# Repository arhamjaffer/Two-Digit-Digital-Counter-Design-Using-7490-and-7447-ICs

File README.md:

# 🔢 Two-Digit Digital Counter Using 7490 & 7447 ICs

<div align="center">

</div>

---

## 📌 Project Overview

This project implements a two-digit decimal counter capable of counting from **00 to 99** using TTL logic ICs.

The design utilizes:

- 7490 Decade Counter IC
- 7447 BCD to Seven Segment Decoder IC
- Common Anode Seven Segment Displays

The counter automatically increments and displays the count on two seven-segment displays.

---

## ⚙️ Components Used

| Component | Quantity |
|------------|----------|
| 7490 Decade Counter IC | 2 |
| 7447 Decoder Driver IC | 2 |
| Common Anode Seven Segment Display | 2 |
| Clock Source | 1 |
| Resistors | Multiple |
| Power Supply (5V) | 1 |

---

## ✨ Features

- Counts from 00 to 99
- Automatic carry generation
- TTL Logic Implementation
- Seven Segment Display Output
- Educational Digital Electronics Project
- Expandable to Higher Digits

---

## 🧠 Working Principle

### Units Counter

The first 7490 counts clock pulses from 0 to 9.

### Tens Counter

After every 10 counts, a carry pulse increments the second 7490.

### Display Driver

Each 7447 converts BCD output into signals for the seven-segment displays.

This allows the count to be displayed as:

```text
00 → 01 → 02 → ... → 98 → 99
```

---

## 📷 Project Gallery

<h2 align="center">📷 Project Gallery</h2>

<h3 align="center">Circuit Schematic</h3>

<h3 align="center">PCB Layout</h3>

<h3 align="center">3D PCB Views</h3>

<table align="center">
<tr>
<td align="center">
<br>
<b>Front View</b>
</td>

<td align="center">
<br>
<b>Back View</b>
</td>
</tr>
</table>
---

## 🎯 Learning Outcomes

✔ Digital Logic Design

✔ BCD Counting

✔ Seven Segment Display Interfacing

✔ TTL Logic Circuits

✔ Hardware Troubleshooting

✔ PCB Design

---

## 🚀 Applications

- Digital Counters
- Frequency Counters
- Event Counters
- Educational Electronics Labs
- Embedded System Prototyping

---

## 👨‍💻 Author

### Arham Jaffer

Electrical Engineering Student

PCB Designer | Embedded Systems Developer | IoT Enthusiast

---

⭐ If you found this project useful, please consider giving it a star.

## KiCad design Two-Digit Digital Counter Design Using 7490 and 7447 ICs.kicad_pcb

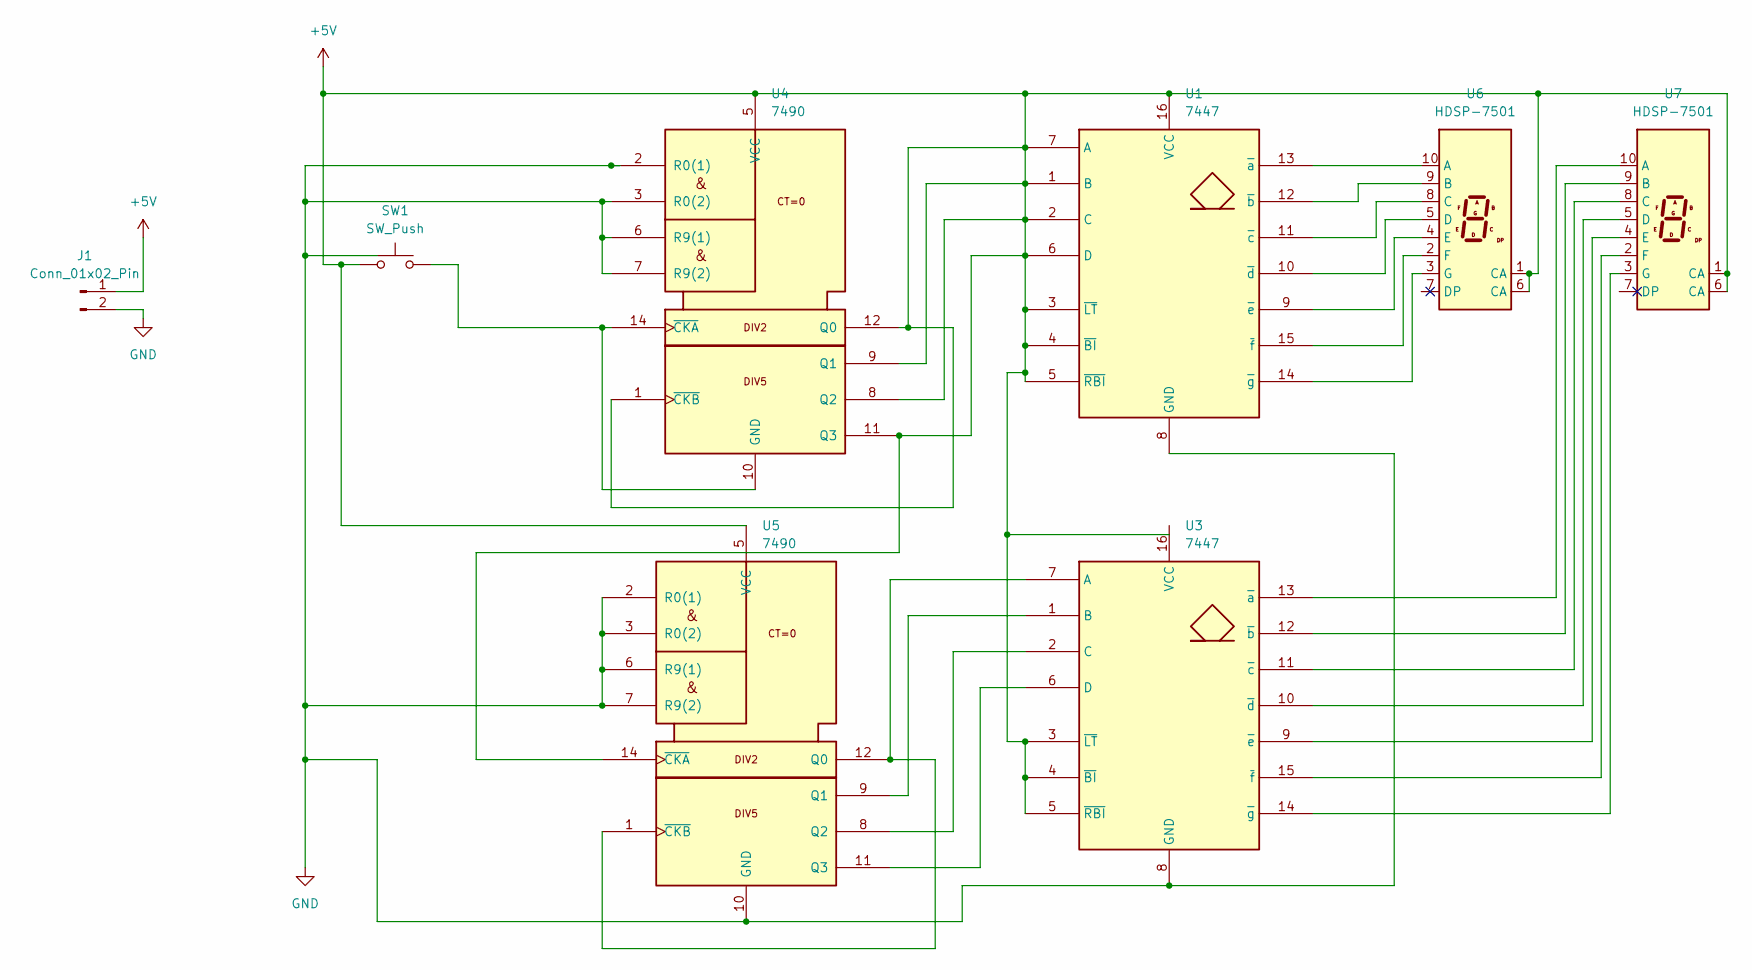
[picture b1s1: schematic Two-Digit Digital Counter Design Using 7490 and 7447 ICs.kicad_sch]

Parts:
J1: Conn_01x02_Pin; PinHeader_1x02_P2.54mm_Vertical
SW1: SW_Push; SW_PUSH_6mm
U1, U3: 7447; DIP-16_W7.62mm
U4, U5: 7490; DIP-14_W7.62mm
U6, U7: HDSP-7501; 7SegmentLED_LTS6760_LTS6780

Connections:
+5V: J1.1, SW1.1, U1.1 (B), U1.2 (C), U1.3 (~LT), U1.4 (~BI), U1.5 (~RBI), U1.6 (D), U1.7 (A), U1.16 (VCC), U3.3 (~LT), U3.4 (~BI), U3.5 (~RBI), U4.1 (~CKB), U4.5 (VCC), U4.8 (Q2), U4.9 (Q1), U4.11 (Q3), U4.12 (Q0), U5.5 (VCC), U5.14 (~CKA), U6.1 (CA), U6.6 (CA), U7.1 (CA), U7.6 (CA)
GND: J1.2, U1.8 (GND), U3.8 (GND), U4.2 (R0(1)), U4.3 (R0(2)), U4.6 (R9(1)), U4.7 (R9(2)), U5.2 (R0(1)), U5.3 (R0(2)), U5.6 (R9(1)), U5.7 (R9(2)), U5.10 (GND)
unnamed: U1.13 (~a), U6.10 (A)
unnamed: U1.12 (~b), U6.9 (B)
unnamed: U1.11 (~c), U6.8 (C)
unnamed: U1.10 (~d), U6.5 (D)
unnamed: U1.9 (~e), U6.4 (E)
unnamed: U1.15 (~f), U6.2 (F)
unnamed: U1.14 (~g), U6.3 (G)
unnamed: U3.7 (A), U5.1 (~CKB), U5.12 (Q0)
unnamed: U3.1 (B), U5.9 (Q1)
unnamed: U3.2 (C), U5.8 (Q2)
unnamed: U3.6 (D), U5.11 (Q3)
unnamed: U3.13 (~a), U7.10 (A)
unnamed: U3.12 (~b), U7.9 (B)
unnamed: U3.11 (~c), U7.8 (C)
unnamed: U3.10 (~d), U7.5 (D)
unnamed: U3.9 (~e), U7.4 (E)
unnamed: U3.15 (~f), U7.2 (F)
unnamed: U3.14 (~g), U7.3 (G)
unnamed: SW1.2, U4.10 (GND), U4.14 (~CKA)

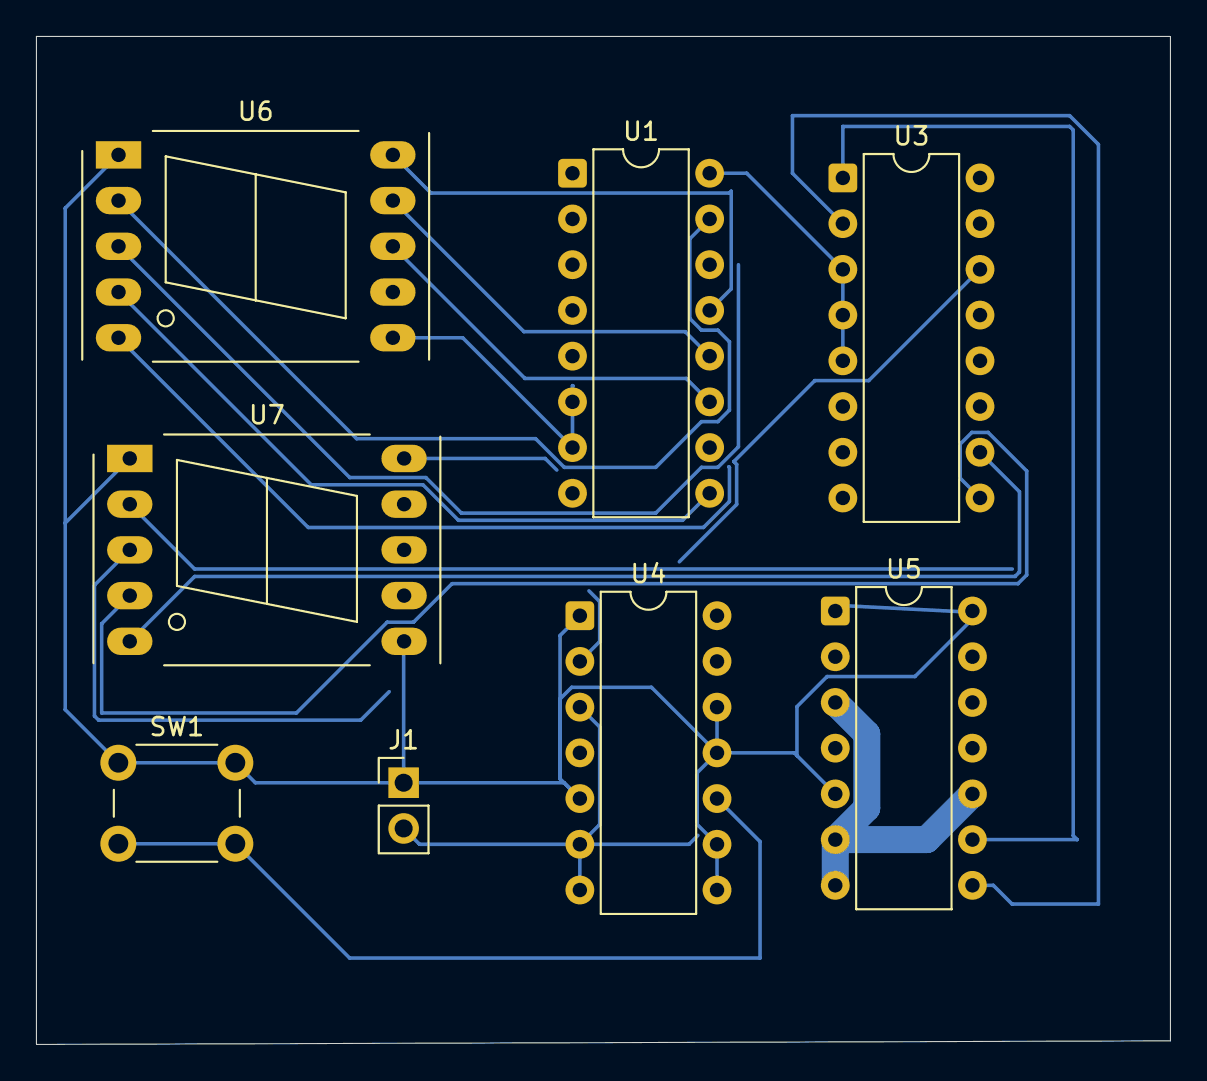
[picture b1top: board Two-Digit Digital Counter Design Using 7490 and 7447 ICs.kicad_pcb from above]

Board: 2 copper layers, 63.0 x 56.0 mm, 8 parts (0 on the bottom side), 21 nets.
